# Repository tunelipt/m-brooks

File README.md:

# m-brooks
Cointroller for brooks thermal mass meters

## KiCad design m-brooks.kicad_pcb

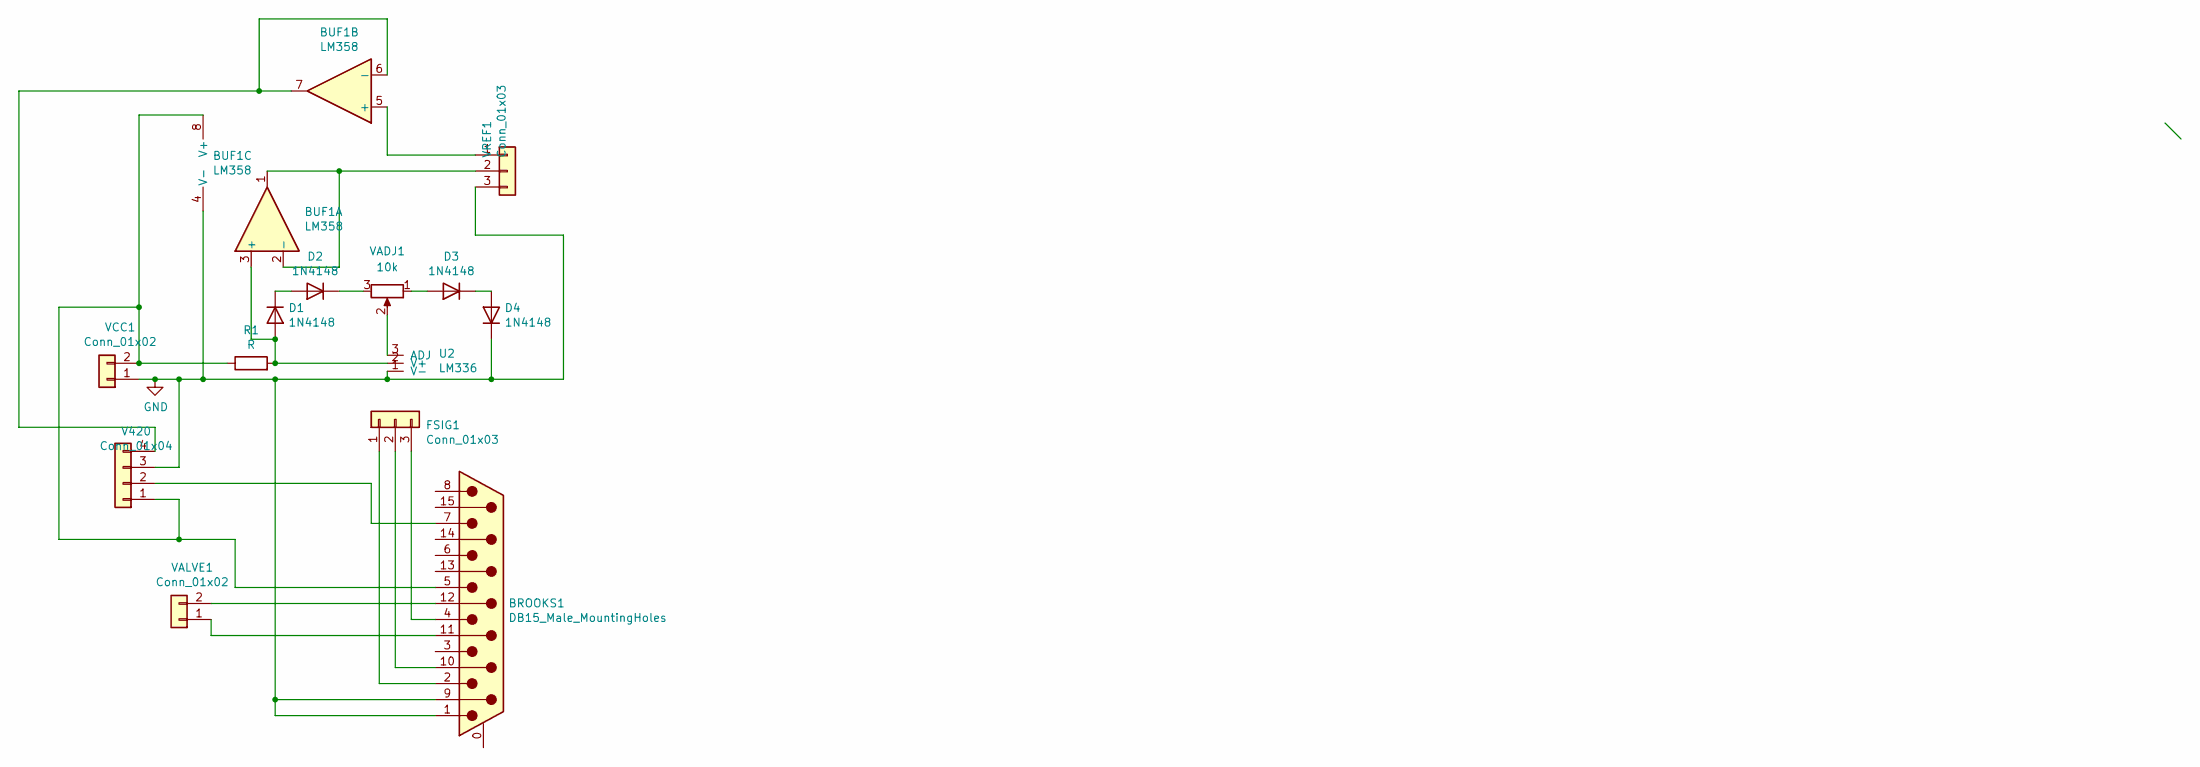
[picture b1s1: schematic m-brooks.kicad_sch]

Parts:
BROOKS1: DB15_Male_MountingHoles; DSUB-15_Female_Horizontal_P2.77x2.84mm_EdgePinOffset7.70mm_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
BUF1: LM358; DIP-8_W7.62mm
D1, D2, D3, D4: 1N4148; D_DO-35_SOD27_P7.62mm_Horizontal
FSIG1: Conn_01x03; TerminalBlock_bornier-3_P5.08mm
R1: R; R_Axial_DIN0207_L6.3mm_D2.5mm_P10.16mm_Horizontal
U2: LM336; TO-92L_Inline_Wide
V420: Conn_01x04; TerminalBlock_bornier-4_P5.08mm
VADJ1: 10k
VALVE1: Conn_01x02; TerminalBlock_bornier-2_P5.08mm
VCC1: Conn_01x02; TerminalBlock_bornier-2_P5.08mm
VREF1: Conn_01x03; TerminalBlock_bornier-3_P5.08mm

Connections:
GND: BROOKS1.1, BROOKS1.9, BUF1.4 (V-), D4.1 (K), U2.1 (V-), V420.3, VCC1.1, VREF1.3
unnamed: BROOKS1.2, FSIG1.1
unnamed: BROOKS1.4, FSIG1.3
unnamed: BROOKS1.5, BUF1.8 (V+), R1.1, V420.1, VCC1.2
unnamed: BROOKS1.7, V420.2
unnamed: BROOKS1.10, FSIG1.2
unnamed: BROOKS1.11 (P111), VALVE1.1
unnamed: BROOKS1.12, VALVE1.2
unnamed: BUF1.1, BUF1.2 (-), VREF1.2
unnamed: BUF1.3 (+), D1.2 (A), R1.2, U2.2 (V+)
unnamed: BUF1.5 (+), VREF1.1
unnamed: BUF1.6 (-), BUF1.7, V420.4
unnamed: D1.1 (K), D2.2 (A)
unnamed: D2.1 (K), VADJ1.3
unnamed: D3.1 (K), D4.2 (A)
unnamed: D3.2 (A), VADJ1.1
unnamed: U2.3 (ADJ), VADJ1.2

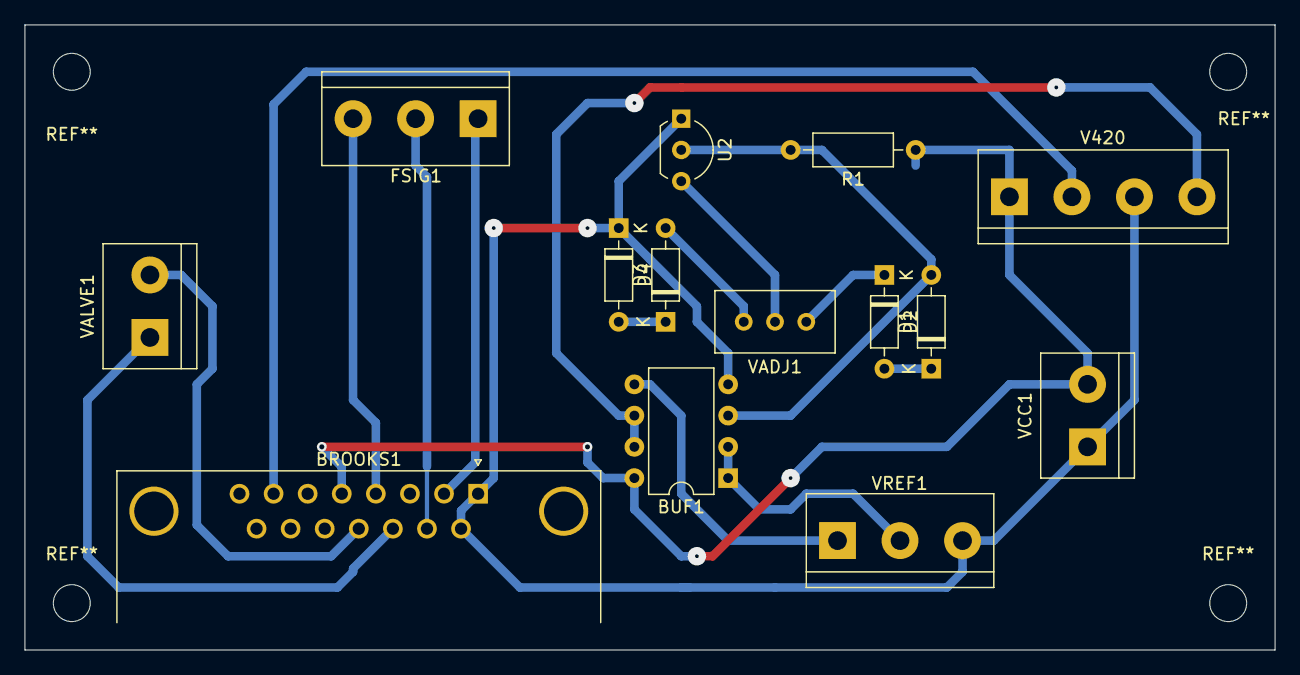
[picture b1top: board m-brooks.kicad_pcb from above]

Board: 2 copper layers, 101.6 x 50.8 mm, 14 parts (0 on the bottom side), 17 nets.

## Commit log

2022-05-18 Added KiCAD files
2022-05-18 Trying to update to KiCAD v6
